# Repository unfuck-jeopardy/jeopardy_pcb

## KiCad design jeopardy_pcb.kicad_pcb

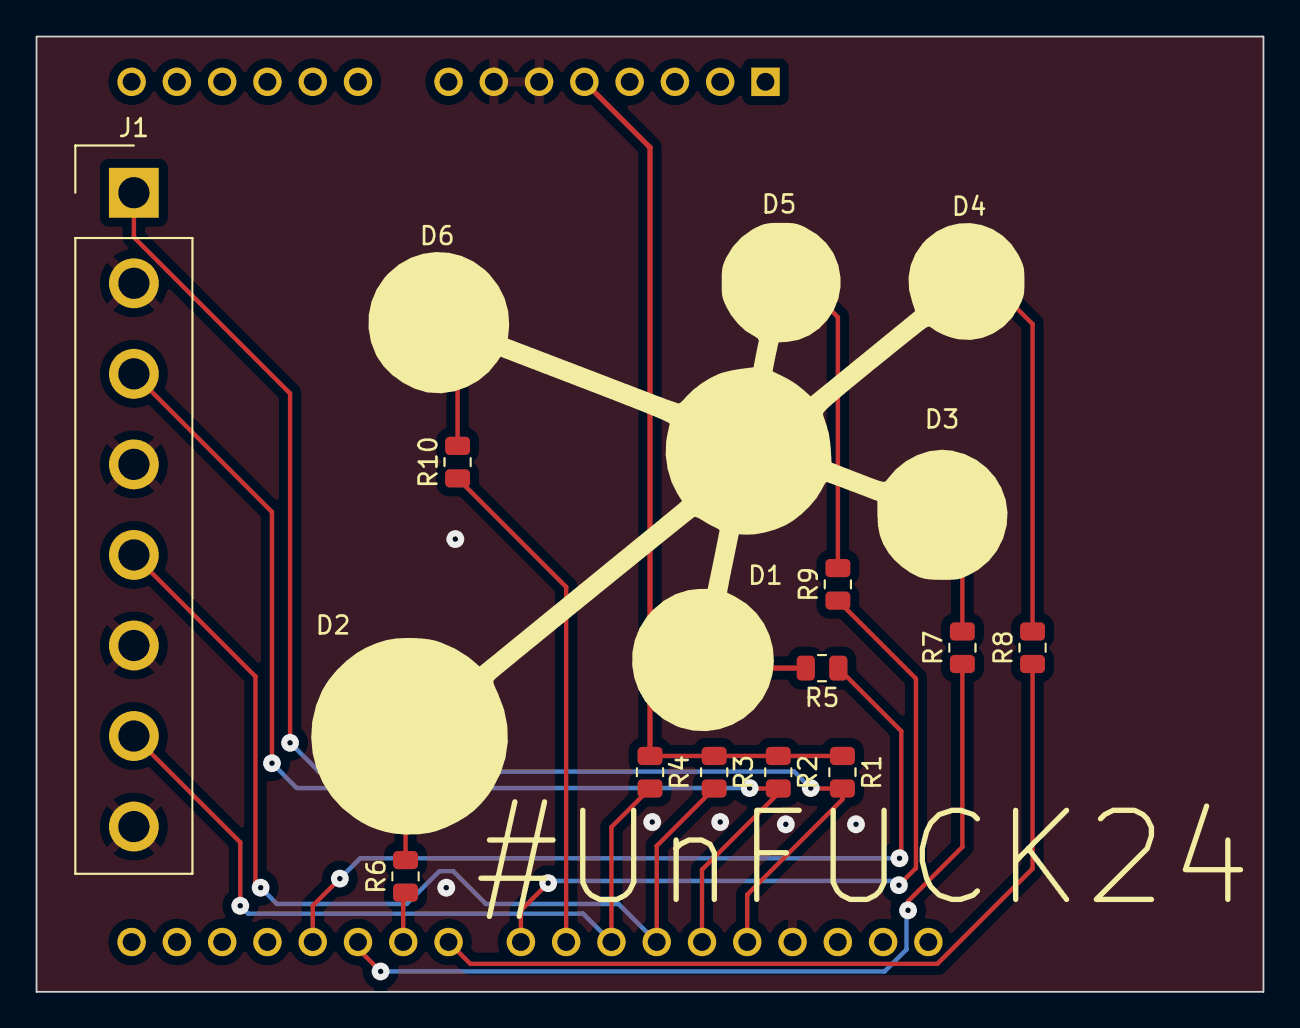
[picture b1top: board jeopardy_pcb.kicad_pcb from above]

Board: 2 copper layers, 68.8 x 53.6 mm, 18 parts (1 on the bottom side), 18 nets.

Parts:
A1: arduino; Arduino_UNO_R3
D1: LED_red; LED_D3.0mm
D2: LED_green; LED_D3.0mm
D3: LED_yellow; LED_D3.0mm
D4: LED_blue; LED_D3.0mm
D5, D6: LED_white; LED_D3.0mm
J1: Conn_Buzzer; Samtec_HPM-08-01-x-S_Straight_1x08_Pitch5.08mm
R1, R2, R3, R4: 10k; R_0805_2012Metric
R5, R8: 300; R_0805_2012Metric
R6, R7, R9, R10: 400; R_0805_2012Metric

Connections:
+5V: A1.5 (+5V), R1.1, R2.1, R3.1, R4.1
A: A1.25 (D10), J1.7, R4.2
B: A1.26 (D11), J1.5, R3.2
C: A1.27 (D12), J1.3, R2.2
D: A1.28 (D13), J1.1, R1.2
GND: A1.6 (GND), A1.7 (GND), A1.29 (GND), D1.1 (K), D2.1 (K), D3.1 (K), D4.1 (K), D5.1 (K), D6.1 (K), J1.2, J1.4, J1.6, J1.8
LED_A: A1.19 (D4), R5.1
LED_B: A1.20 (D5), R7.1
LED_C: A1.21 (D6), R6.1
LED_D: A1.22 (D7), R8.1
LED_E: A1.23 (D8), R9.1
LED_F: A1.24 (D9), R10.1
unnamed: D1.2 (A), R5.2
unnamed: D2.2 (A), R6.2
unnamed: D3.2 (A), R7.2
unnamed: D4.2 (A), R8.2
unnamed: D5.2 (A), R9.2
unnamed: D6.2 (A), R10.2

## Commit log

2024-04-27 Initial commit #UnFUCK24 version.
